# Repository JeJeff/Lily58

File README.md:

# Lily58
Lily58 is 6*4+4keys column-staggered split keyboard.

This fork adds the Lily58 Ultra, which uses through-hole diodes and adds MX hotswap sockets, per-key and/or backlight LEDs, and rotary encoder support.  

## [Document Site Here](https://kata0510.github.io/Lily58-Document/)

# Type

- Lily58 Pro
  - [PCB Data](https://github.com/kata0510/Lily58/tree/master/Pro/PCB)
  - [BuildGuide JP](https://kata0510.github.io/Lily58-Document/Lily58_Pro.html)
  - [BuildGuide EN](https://kata0510.github.io/Lily58-Document/Lily58_Pro_BG_ENG.html)
  - [Shop(Yushakobo)](https://yushakobo.jp/shop/lily58-pro/)
- Lily58 Lite Rev2
  - [BuildGuide(YouTube)](https://www.youtube.com/watch?v=t6HLQvqlsVM)
  - [BuildInfo](https://kata0510.github.io/Lily58-Document/Lily58_Lite_Rev2.html)
  - [Shop(BOOTH)](https://booth.pm/ja/items/1963895)
  - [Shop(Yushakobo)](https://yushakobo.jp/shop/consign_lily58-lite-rev2/)
- Lily58(Old)
  - [PCB Data](https://github.com/kata0510/Lily58/tree/master/pcb)
  - [BuildGuide](https://kata0510.github.io/Lily58-Document/Lily58_BG.html)
- Lily58 Lite Rev1(Old)
  - [PCB Data](https://github.com/kata0510/Lily58/tree/master/pcb)
  - [BuildGuide](https://kata0510.github.io/Lily58-Document/Lily58_Lite_BG.html)

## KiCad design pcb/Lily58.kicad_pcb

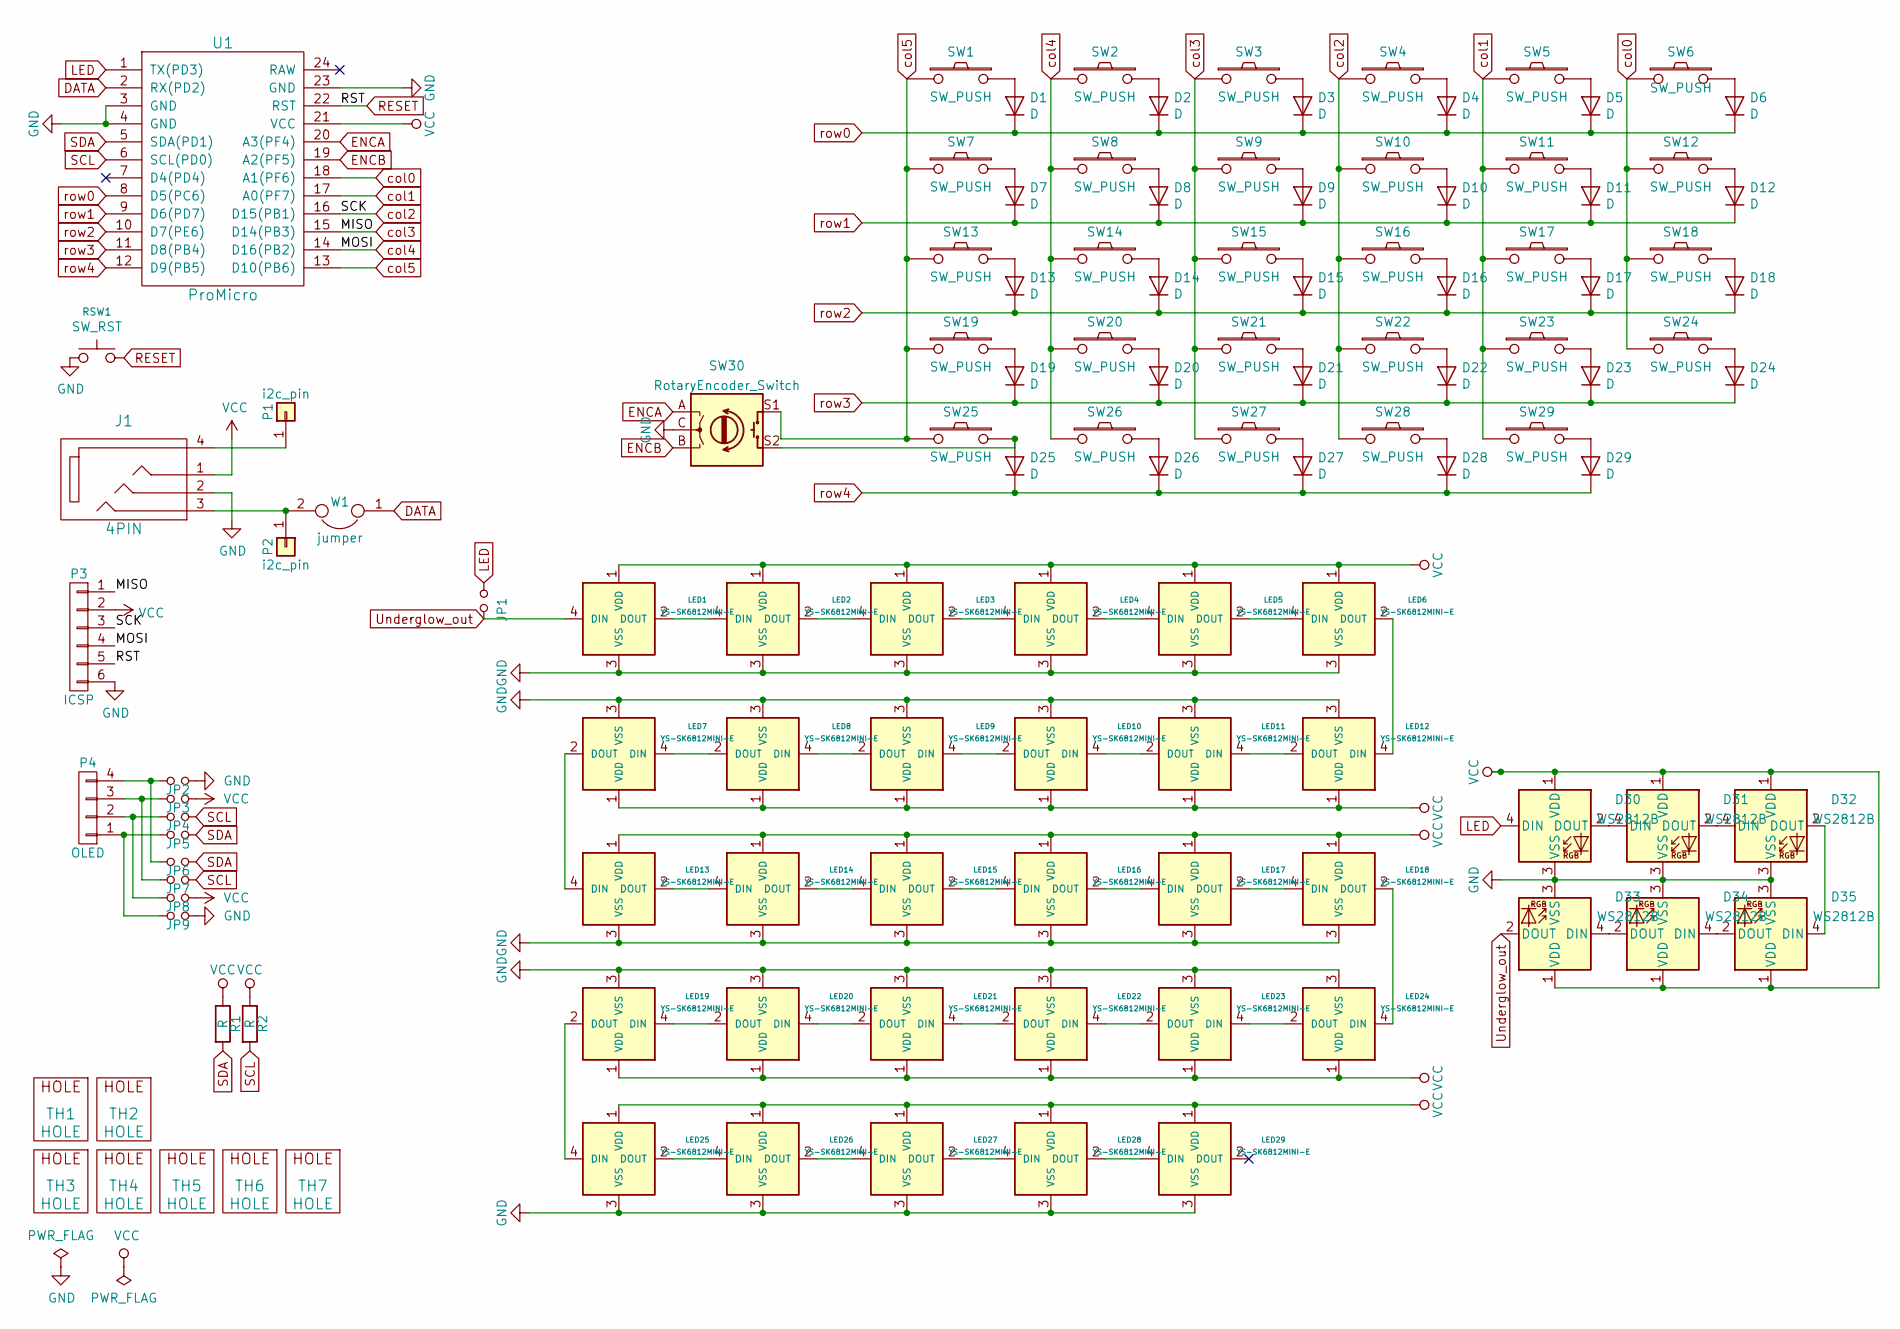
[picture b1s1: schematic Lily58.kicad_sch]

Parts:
D1, D2, D3, D4, D5, D6, D7, D8, D9, D10, D11, D12, D13, D14, D15, D16, D17, D18, D19, D20, D21, D22, D23, D24, D25, D26, D27, D28, D29: D; Diode-Doublesided-TH-7.5mm
D30, D31, D32, D33, D34, D35: WS2812B; WS2812B-double sided
J1: 4PIN; MJ-4PP-9
JP1, JP2, JP3, JP4, JP5, JP6, JP7, JP8, JP9: Jumper_NO_Small; Jumper
LED1, LED2, LED3, LED4, LED5, LED6, LED7, LED8, LED9, LED10, LED11, LED12, LED13, LED14, LED15, LED16, LED17, LED18, LED19, LED20, LED21, LED22, LED23, LED24, LED25, LED26, LED27, LED28, LED29: YS-SK6812MINI-E; SK6812MINI-E
P1, P2: i2c_pin; 1pin_conn
P3: ICSP
P4: OLED; MY_SIL-4
R1, R2: R; RESISTOR_mini
RSW1: SW_RST; TACT_SWITCH_TVBP06
SW1, SW2, SW3, SW4, SW5, SW6, SW7, SW8, SW9, SW10, SW11, SW12, SW13, SW14, SW15, SW16, SW17, SW18, SW19, SW20, SW21, SW22, SW23, SW24, SW25, SW26, SW27, SW28, SW29: SW_PUSH; MX_Socket_18mm
SW30: RotaryEncoder_Switch; RotaryEncoder_EC11-no-legs_noSS
TH1, TH2: HOLE; HOLE_M2
TH3, TH4, TH5, TH6, TH7: HOLE; HOLE_M2_TH
U1: ProMicro; ProMicro_rev2
W1: jumper; jumper_data

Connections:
DATA: U1.2 (RX(PD2)), W1.1
ENCA: SW30.A, U1.20 (A3(PF4))
ENCB: SW30.B, U1.19 (A2(PF5))
GND: D30.3 (VSS), D31.3 (VSS), D32.3 (VSS), D33.3 (VSS), D34.3 (VSS), D35.3 (VSS), J1.2, JP2.2, JP9.2, LED1.3 (VSS), LED2.3 (VSS), LED3.3 (VSS), LED4.3 (VSS), LED5.3 (VSS), LED6.3 (VSS), LED7.3 (VSS), LED8.3 (VSS), LED9.3 (VSS), LED10.3 (VSS), LED11.3 (VSS), LED12.3 (VSS), LED13.3 (VSS), LED14.3 (VSS), LED15.3 (VSS), LED16.3 (VSS), LED17.3 (VSS), LED18.3 (VSS), LED19.3 (VSS), LED20.3 (VSS), LED21.3 (VSS), LED22.3 (VSS), LED23.3 (VSS), LED24.3 (VSS), LED25.3 (VSS), LED26.3 (VSS), LED27.3 (VSS), LED28.3 (VSS), LED29.3 (VSS), P3.6, RSW1.1, SW30.C, U1.3 (GND), U1.4 (GND), U1.23 (GND)
LED: D30.4 (DIN), JP1.2, U1.1 (TX(PD3))
unnamed: D1.2 (A), SW1.2
unnamed: D2.2 (A), SW2.2
unnamed: D3.2 (A), SW3.2
unnamed: D4.2 (A), SW4.2
unnamed: D5.2 (A), SW5.2
unnamed: D6.2 (A), SW6.2
unnamed: D7.2 (A), SW7.2
unnamed: D8.2 (A), SW8.2
unnamed: D9.2 (A), SW9.2
unnamed: D10.2 (A), SW10.2
unnamed: D11.2 (A), SW11.2
unnamed: D12.2 (A), SW12.2
unnamed: D13.2 (A), SW13.2
unnamed: D14.2 (A), SW14.2
unnamed: D15.2 (A), SW15.2
unnamed: D16.2 (A), SW16.2
unnamed: D17.2 (A), SW17.2
unnamed: D18.2 (A), SW18.2
unnamed: D19.2 (A), SW19.2
unnamed: D20.2 (A), SW20.2
unnamed: D21.2 (A), SW21.2
unnamed: D22.2 (A), SW22.2
unnamed: D23.2 (A), SW23.2
unnamed: D24.2 (A), SW24.2
unnamed: D25.2 (A), SW25.2, SW30.S2
unnamed: D26.2 (A), SW26.2
unnamed: D27.2 (A), SW27.2
unnamed: D28.2 (A), SW28.2
unnamed: D29.2 (A), SW29.2
unnamed: D30.2 (DOUT), D31.4 (DIN)
unnamed: D31.2 (DOUT), D32.4 (DIN)
unnamed: D32.2 (DOUT), D35.4 (DIN)
unnamed: D33.4 (DIN), D34.2 (DOUT)
unnamed: D34.4 (DIN), D35.2 (DOUT)
unnamed: J1.3, P2.1, W1.2
unnamed: J1.4, P1.1
unnamed: JP2.1, JP6.1, P4.4
unnamed: JP3.1, JP7.1, P4.3
unnamed: JP4.1, JP8.1, P4.2
unnamed: JP5.1, JP9.1, P4.1
unnamed: LED1.2 (DOUT), LED2.4 (DIN)
unnamed: LED2.2 (DOUT), LED3.4 (DIN)
unnamed: LED3.2 (DOUT), LED4.4 (DIN)
unnamed: LED4.2 (DOUT), LED5.4 (DIN)
unnamed: LED5.2 (DOUT), LED6.4 (DIN)
unnamed: LED7.4 (DIN), LED8.2 (DOUT)
unnamed: LED8.4 (DIN), LED9.2 (DOUT)
unnamed: LED9.4 (DIN), LED10.2 (DOUT)
unnamed: LED10.4 (DIN), LED11.2 (DOUT)
unnamed: LED11.4 (DIN), LED12.2 (DOUT)
unnamed: LED6.2 (DOUT), LED12.4 (DIN)
unnamed: LED13.2 (DOUT), LED14.4 (DIN)
unnamed: LED7.2 (DOUT), LED13.4 (DIN)
unnamed: LED14.2 (DOUT), LED15.4 (DIN)
unnamed: LED15.2 (DOUT), LED16.4 (DIN)
unnamed: LED16.2 (DOUT), LED17.4 (DIN)
unnamed: LED17.2 (DOUT), LED18.4 (DIN)
unnamed: LED18.2 (DOUT), LED24.4 (DIN)
unnamed: LED19.2 (DOUT), LED25.4 (DIN)
unnamed: LED19.4 (DIN), LED20.2 (DOUT)
unnamed: LED20.4 (DIN), LED21.2 (DOUT)
unnamed: LED21.4 (DIN), LED22.2 (DOUT)
unnamed: LED22.4 (DIN), LED23.2 (DOUT)
unnamed: LED23.4 (DIN), LED24.2 (DOUT)
unnamed: LED25.2 (DOUT), LED26.4 (DIN)
unnamed: LED26.2 (DOUT), LED27.4 (DIN)
unnamed: LED27.2 (DOUT), LED28.4 (DIN)
unnamed: LED28.2 (DOUT), LED29.4 (DIN)
RESET: P3.5, RSW1.2, U1.22 (RST)
SCL: JP4.2, JP7.2, R2.2, U1.6 (SCL(PD0))
SDA: JP5.2, JP6.2, R1.2, U1.5 (SDA(PD1))
Underglow_out: D33.2 (DOUT), JP1.1, LED1.4 (DIN)
VCC: D30.1 (VDD), D31.1 (VDD), D32.1 (VDD), D33.1 (VDD), D34.1 (VDD), D35.1 (VDD), J1.1, JP3.2, JP8.2, LED1.1 (VDD), LED2.1 (VDD), LED3.1 (VDD), LED4.1 (VDD), LED5.1 (VDD), LED6.1 (VDD), LED7.1 (VDD), LED8.1 (VDD), LED9.1 (VDD), LED10.1 (VDD), LED11.1 (VDD), LED12.1 (VDD), LED13.1 (VDD), LED14.1 (VDD), LED15.1 (VDD), LED16.1 (VDD), LED17.1 (VDD), LED18.1 (VDD), LED19.1 (VDD), LED20.1 (VDD), LED21.1 (VDD), LED22.1 (VDD), LED23.1 (VDD), LED24.1 (VDD), LED25.1 (VDD), LED26.1 (VDD), LED27.1 (VDD), LED28.1 (VDD), LED29.1 (VDD), P3.2, R1.1, R2.1, U1.21 (VCC)
col0: SW6.1, SW12.1, SW18.1, SW24.1, U1.18 (A1(PF6))
col1: SW5.1, SW11.1, SW17.1, SW23.1, SW29.1, U1.17 (A0(PF7))
col2: P3.3, SW4.1, SW10.1, SW16.1, SW22.1, SW28.1, U1.16 (D15(PB1))
col3: P3.1, SW3.1, SW9.1, SW15.1, SW21.1, SW27.1, U1.15 (D14(PB3))
col4: P3.4, SW2.1, SW8.1, SW14.1, SW20.1, SW26.1, U1.14 (D16(PB2))
col5: SW1.1, SW7.1, SW13.1, SW19.1, SW25.1, SW30.S1, U1.13 (D10(PB6))
row0: D1.1 (K), D2.1 (K), D3.1 (K), D4.1 (K), D5.1 (K), D6.1 (K), U1.8 (D5(PC6))
row1: D7.1 (K), D8.1 (K), D9.1 (K), D10.1 (K), D11.1 (K), D12.1 (K), U1.9 (D6(PD7))
row2: D13.1 (K), D14.1 (K), D15.1 (K), D16.1 (K), D17.1 (K), D18.1 (K), U1.10 (D7(PE6))
row3: D19.1 (K), D20.1 (K), D21.1 (K), D22.1 (K), D23.1 (K), D24.1 (K), U1.11 (D8(PB4))
row4: D25.1 (K), D26.1 (K), D27.1 (K), D28.1 (K), D29.1 (K), U1.12 (D9(PB5))

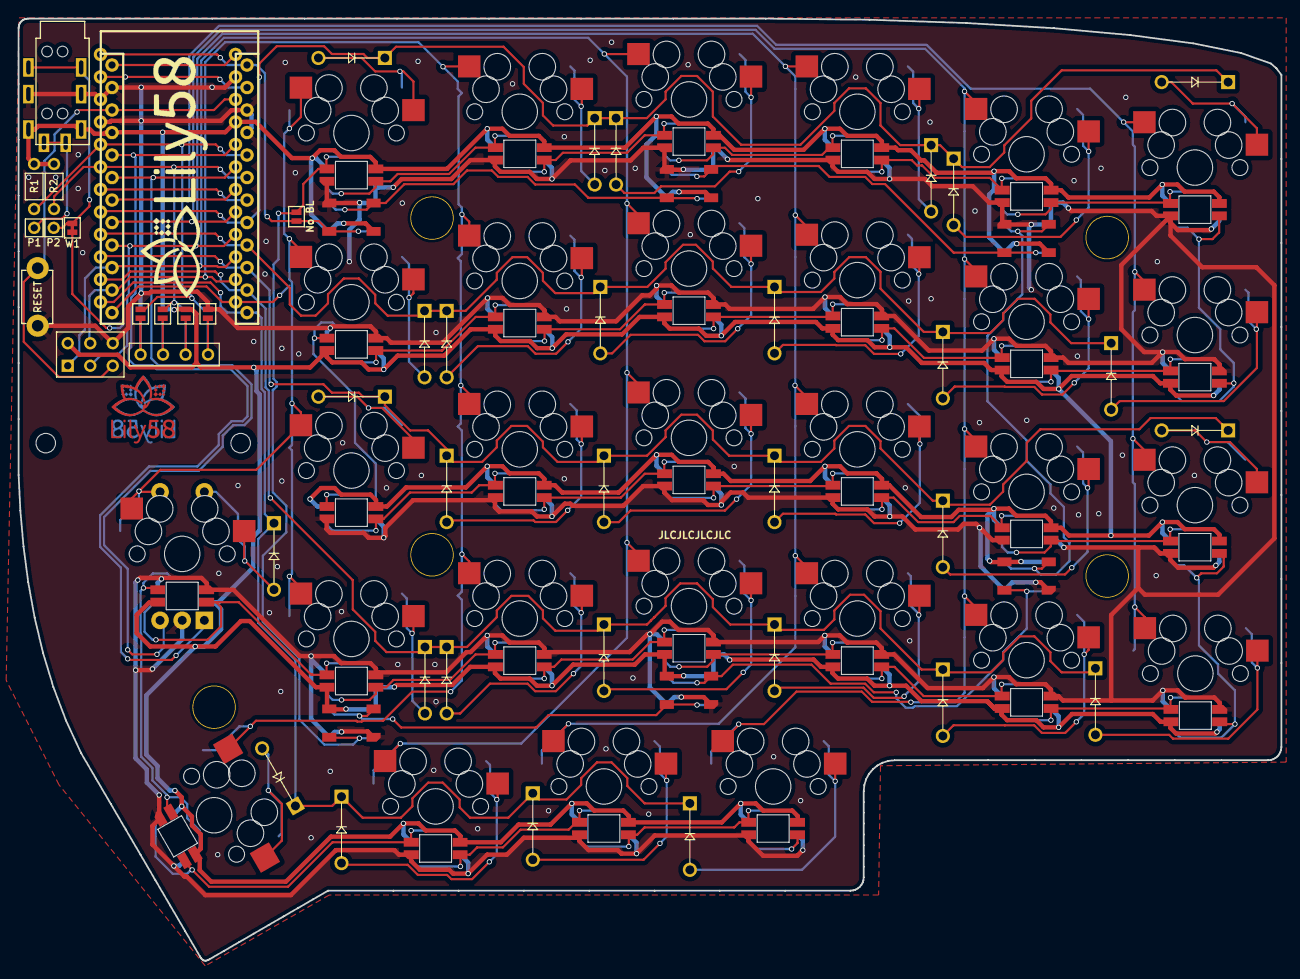
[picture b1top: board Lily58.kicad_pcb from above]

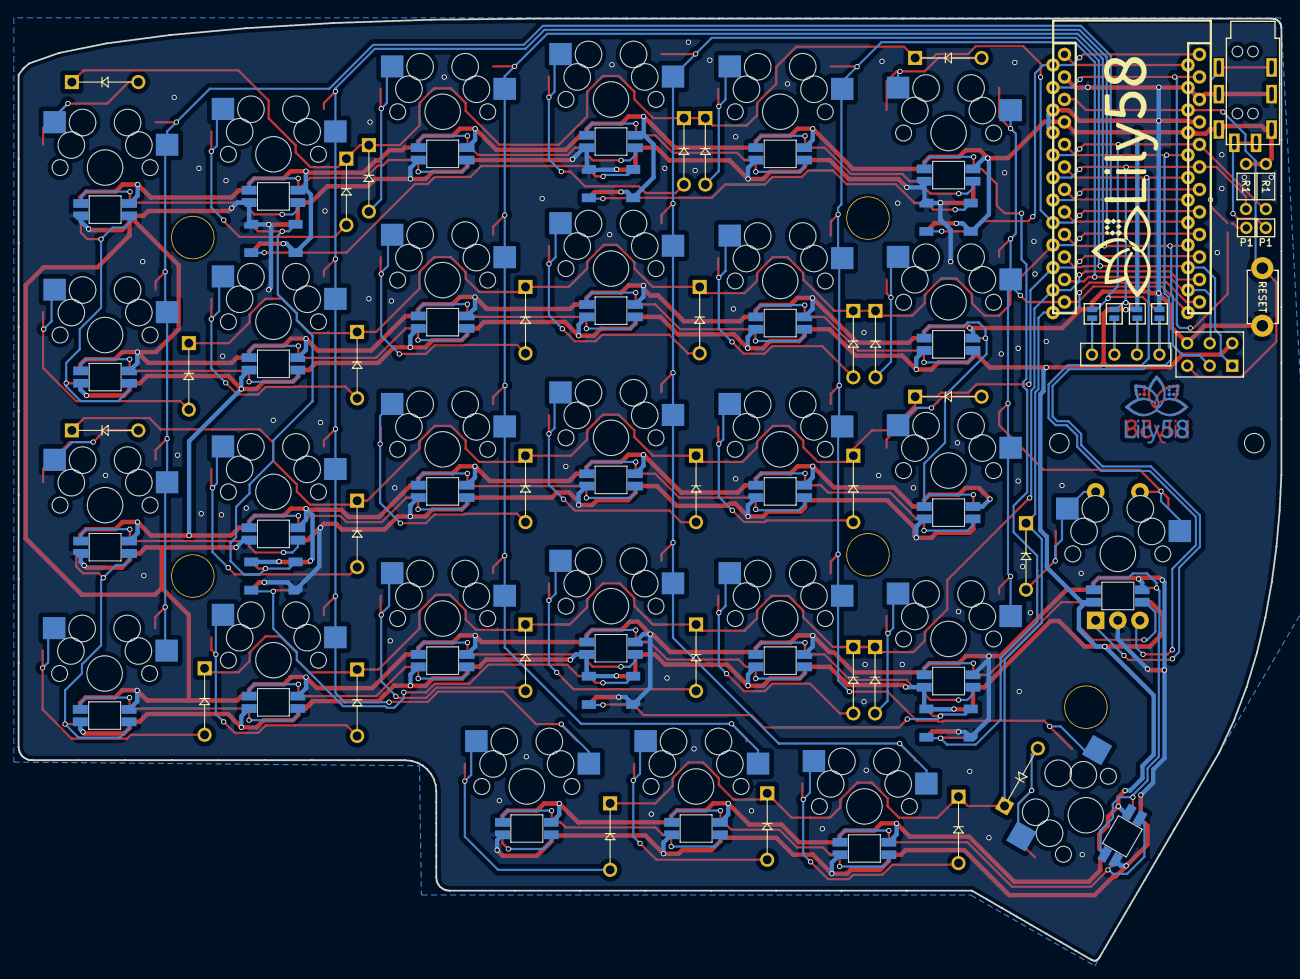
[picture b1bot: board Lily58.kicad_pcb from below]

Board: 2 copper layers, 142.5 x 106.3 mm, 120 parts (5 on the bottom side), 89 nets.

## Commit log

2022-01-25 First version for prototyping
2022-01-25 Revert non-ultra changes from "First version for prototyping"
    This partially reverts commit a3e54aa417d9b9a440498bf4f6e0d923b4cb8ab2.
2022-01-25 Update LICENSE
2022-01-25 Clean up triangle above bottom thumb key
    Cases have trouble covering this, so keep it as bare as possible.
2022-01-25 Don't store automatic backups on github
2022-01-26 Minor routing tweaks
